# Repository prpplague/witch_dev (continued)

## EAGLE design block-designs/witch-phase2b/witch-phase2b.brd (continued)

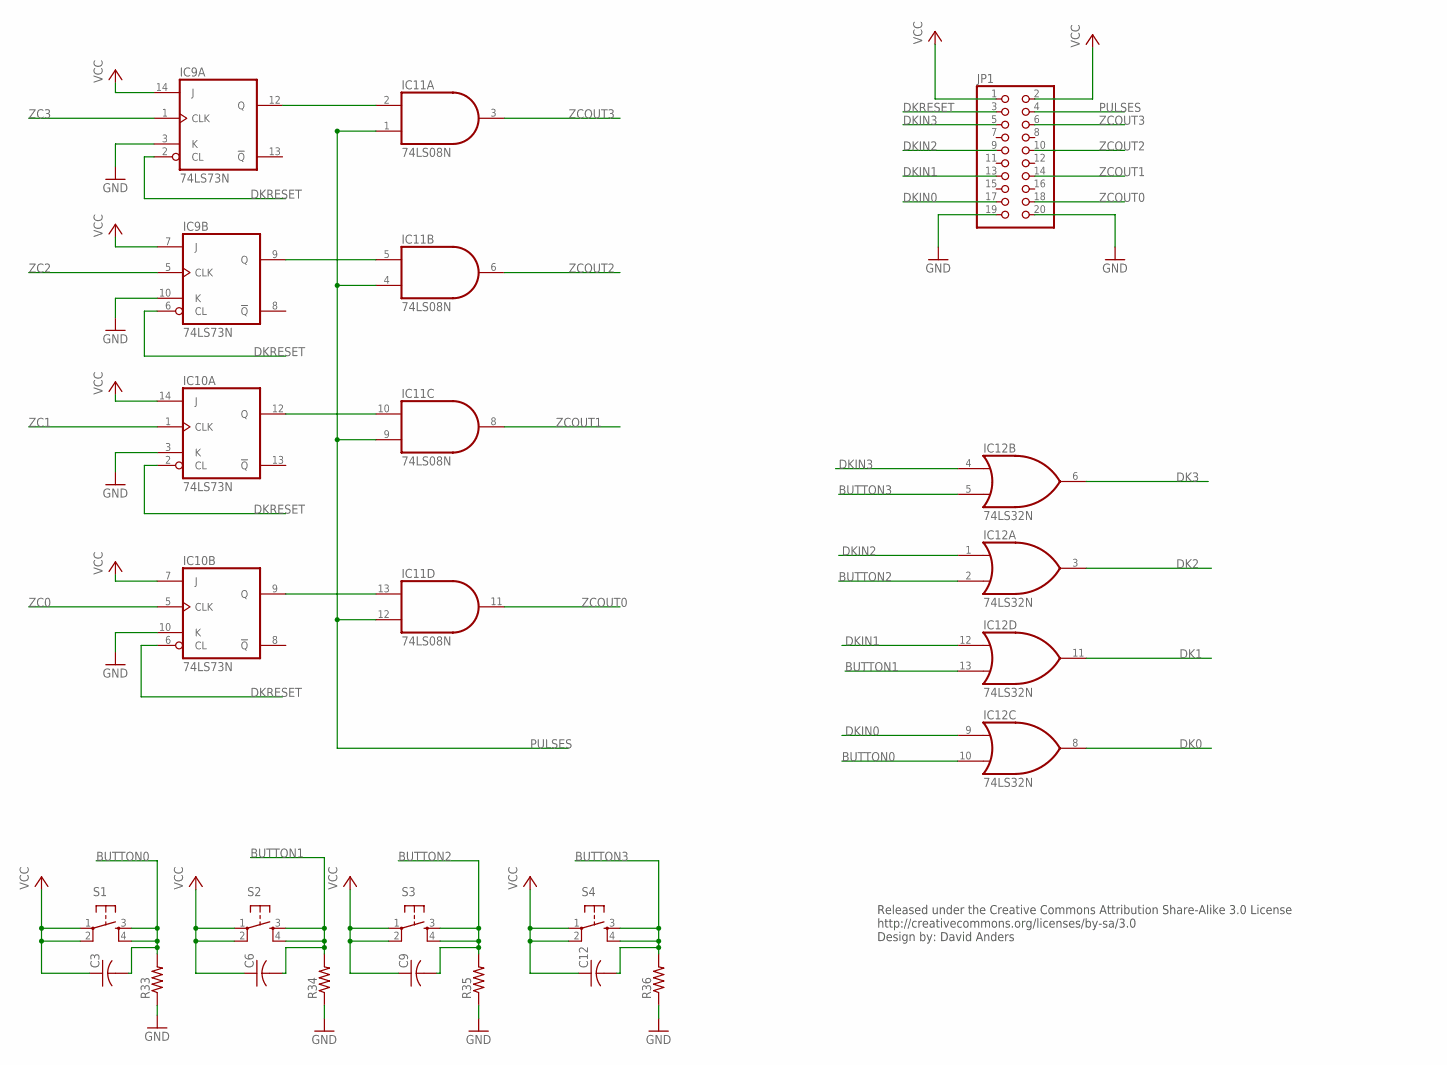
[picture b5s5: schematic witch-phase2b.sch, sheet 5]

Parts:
C3, C6, C9, C12: C-US025-025X050; C025-025X050
IC9, IC10: 74LS73N; DIL14
IC11: 74LS08N; DIL14
IC12: 74LS32N; DIL14
JP1: PINHD-2X10; 2X10
R33, R34, R35, R36: R-US_0204/5; 0204/5
S1, S2, S3, S4: TAC_SWITCHPTH; TACTILE-PTH

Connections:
BUTTON0: C3.2, IC12.10 (I1), R33.2, S1.3, S1.4
BUTTON1: C6.2, IC12.13 (I1), R34.2, S2.3, S2.4
BUTTON2: C9.2, IC12.2 (I1), R35.2, S3.3, S3.4
BUTTON3: C12.2, IC12.5 (I1), R36.2, S4.3, S4.4
DK0: IC12.8 (O); also elsewhere on the board
DK1: IC12.11 (O); also elsewhere on the board
DK2: IC12.3 (O); also elsewhere on the board
DK3: IC12.6 (O); also elsewhere on the board
DKIN0: IC12.9 (I0), JP1.17
DKIN1: IC12.12 (I0), JP1.13
DKIN2: IC12.1 (I0), JP1.9
DKIN3: IC12.4 (I0), JP1.5
DKRESET: IC9.2 (CL), IC9.6 (CL), IC10.2 (CL), IC10.6 (CL), JP1.3
GND: IC9.3 (K), IC9.10 (K), IC10.3 (K), IC10.10 (K), JP1.19, JP1.20, R33.1, R34.1, R35.1, R36.1; also elsewhere on the board
unnamed: IC9.12 (Q), IC11.2 (I1)
unnamed: IC9.9 (Q), IC11.5 (I1)
unnamed: IC10.12 (Q), IC11.10 (I1)
unnamed: IC10.9 (Q), IC11.13 (I1)
PULSES: IC11.1 (I0), IC11.4 (I0), IC11.9 (I0), IC11.12 (I0), JP1.4
VCC: C3.1, IC9.7 (J), IC9.14 (J), IC10.7 (J), IC10.14 (J), JP1.1, JP1.2, S1.1, S1.2, S2.1, S2.2, S3.1, S3.2, S4.1, S4.2; also elsewhere on the board
VCC1: C6.1
VCC2: C9.1
VCC3: C12.1
ZC0: IC10.5 (CLK); also elsewhere on the board
ZC1: IC10.1 (CLK); also elsewhere on the board
ZC2: IC9.5 (CLK); also elsewhere on the board
ZC3: IC9.1 (CLK); also elsewhere on the board
ZCOUT0: IC11.11 (O), JP1.18
ZCOUT1: IC11.8 (O), JP1.14
ZCOUT2: IC11.6 (O), JP1.10
ZCOUT3: IC11.3 (O), JP1.6

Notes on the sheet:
Released under the Creative Commons Attribution Share-Alike 3.0 License http://creativecommons.org/licenses/by-sa/3.0 Design by: David Anders

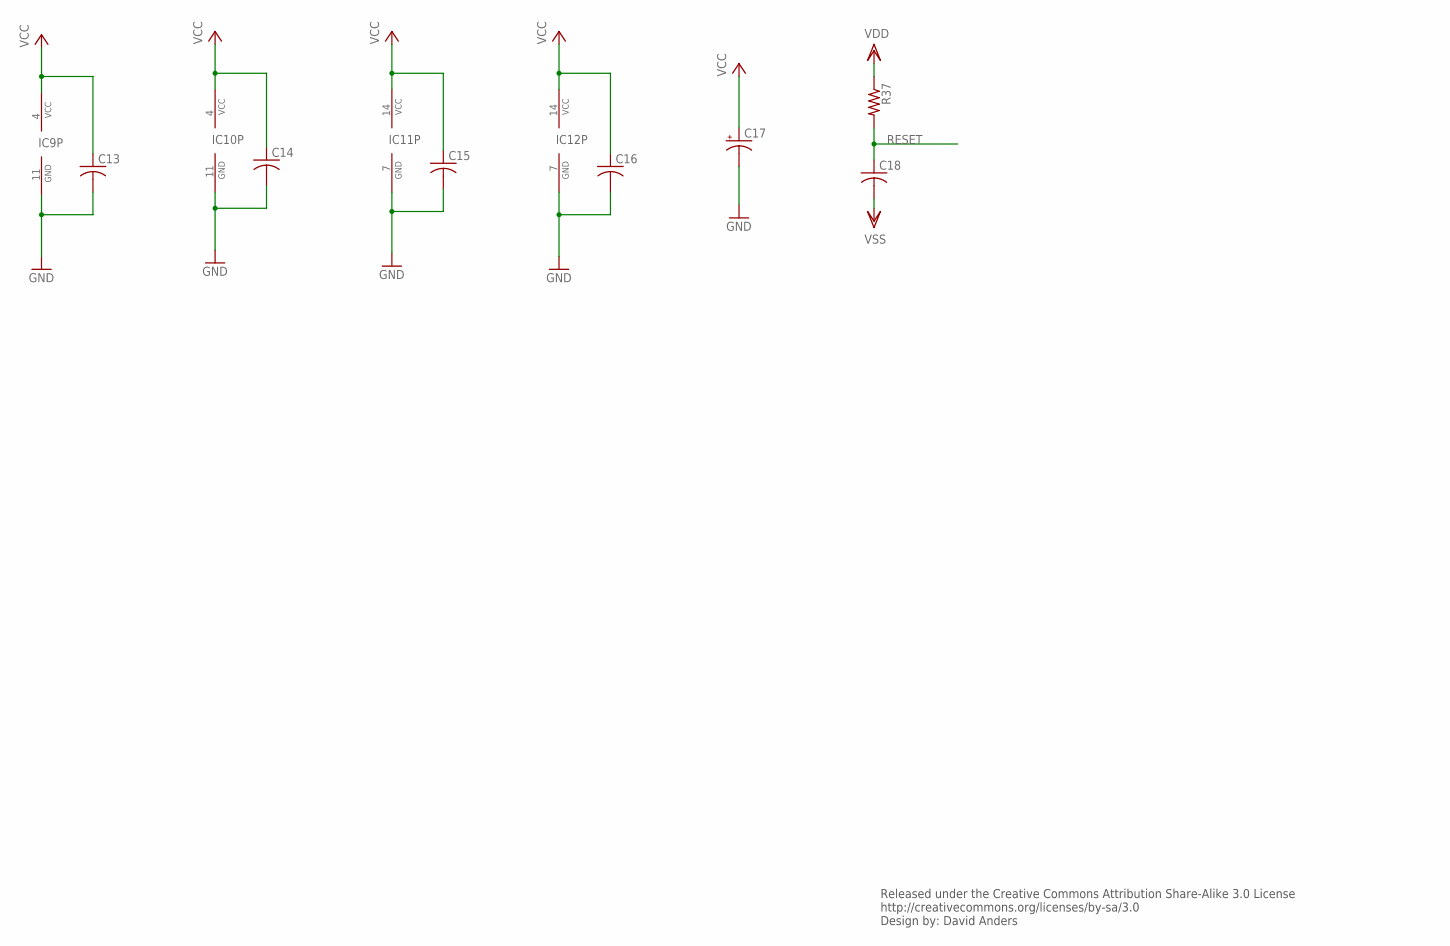
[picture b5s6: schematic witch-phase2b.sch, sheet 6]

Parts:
C13, C14, C15, C16: C-US025-025X050; C025-025X050
C17: CPOL-USE2-5; E2-5
C18: C-US025-040X050; C025-040X050
IC9, IC10: 74LS73N; DIL14
IC11: 74LS08N; DIL14
IC12: 74LS32N; DIL14
R37: R-US_0204/5; 0204/5

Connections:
GND: C13.2, C14.2, C15.2, C16.2, C17.-, IC9.11 (GND), IC10.11 (GND), IC11.7 (GND), IC12.7 (GND); also elsewhere on the board
RESET: C18.1, R37.2; also elsewhere on the board
VCC: C13.1, C14.1, C15.1, C16.1, C17.+, IC9.4 (VCC), IC10.4 (VCC), IC11.14 (VCC), IC12.14 (VCC); also elsewhere on the board
VDD: R37.1
VSS: C18.2

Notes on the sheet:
Released under the Creative Commons Attribution Share-Alike 3.0 License http://creativecommons.org/licenses/by-sa/3.0 Design by: David Anders

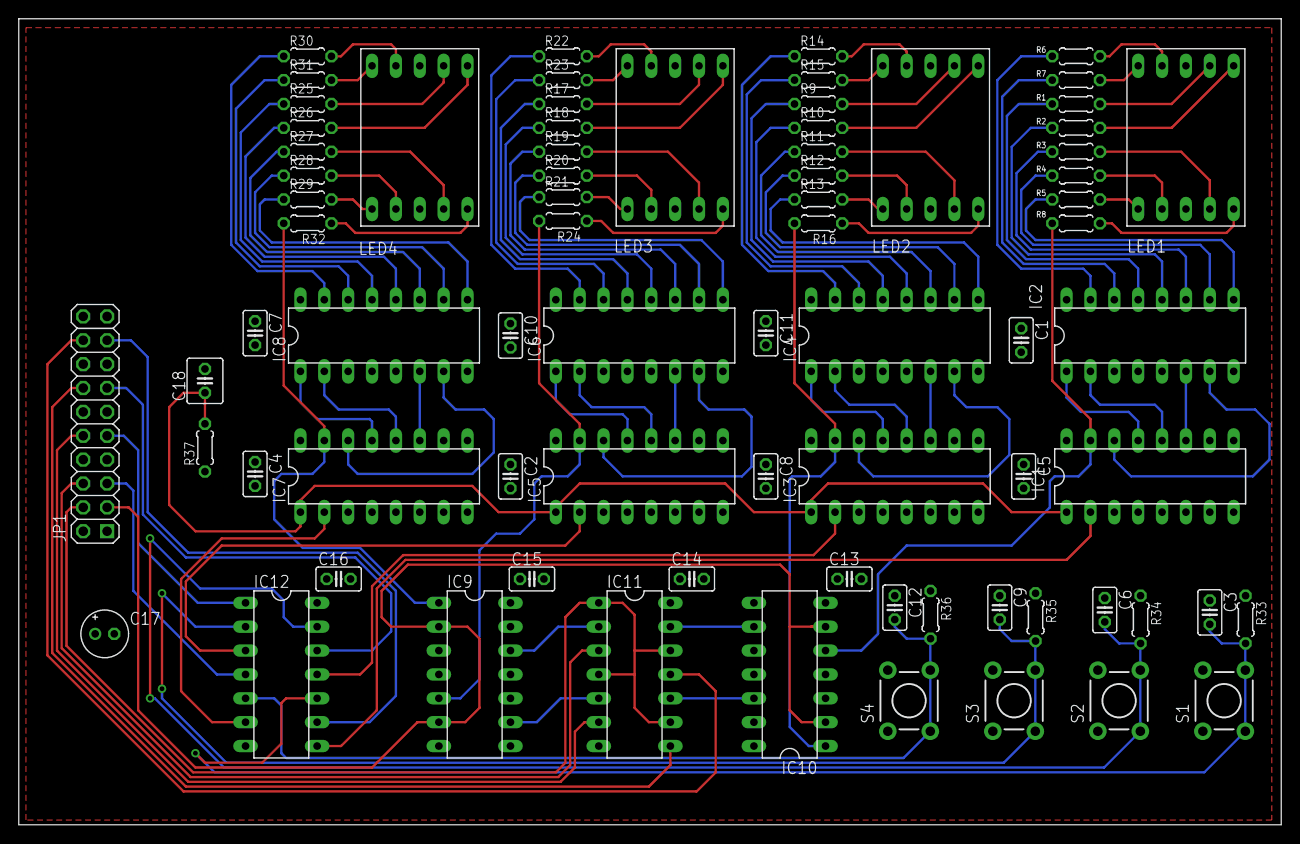
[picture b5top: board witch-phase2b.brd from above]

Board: 2 copper layers, 134.3 x 85.8 mm, 76 parts (0 on the bottom side), 105 nets.

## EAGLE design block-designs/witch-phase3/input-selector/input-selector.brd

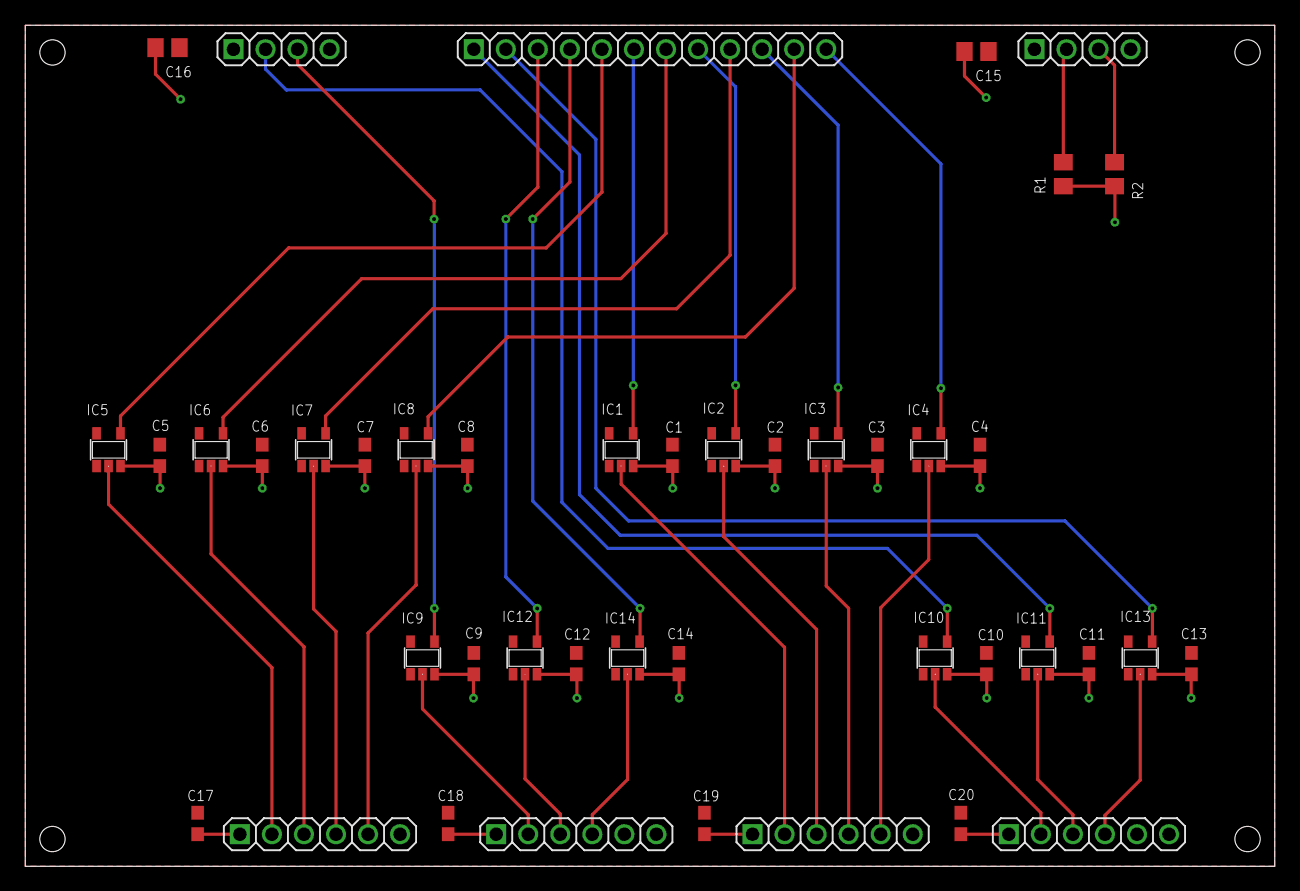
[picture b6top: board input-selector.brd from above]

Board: 2 copper layers, 99.1 x 66.7 mm, 43 parts (0 on the bottom side), 32 nets.

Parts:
C1, C2, C3, C4, C5, C6, C7, C8, C9, C10, C11, C12, C13, C14, C17, C18, C19, C20: C0603
C15, C16: C0805
IC1, IC2, IC3, IC4, IC5, IC6, IC7, IC8, IC9, IC10, IC11, IC12, IC13, IC14: 74LVC1G17DBV; SOT23-5
JP1, JP2, JP3, JP4: 1X06
JP5, JP7: 1X04
JP6: 1X12
R1, R2: R0805

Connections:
GND: C1.2, C2.2, C3.2, C4.2, C5.2, C6.2, C7.2, C8.2, C9.2, C10.2, C11.2, C12.2, C13.2, C14.2, C15.2, C16.2, C17.2, C18.2, C19.2, C20.2, IC1.3, IC2.3, IC3.3, IC4.3, IC5.3, IC6.3, IC7.3, IC8.3, IC9.3, IC10.3, IC11.3, IC12.3, IC13.3, IC14.3, JP1.1, JP2.1, JP3.1, JP4.1, JP5.4, JP7.4, R1.1, R2.1
RCV_ENABLE: JP7.3, R2.2
RCV_ROW0: IC5.4, JP6.5
RCV_ROW1: IC6.4, JP6.7
RCV_ROW2: IC7.4, JP6.9
RCV_ROW3: IC8.4, JP6.11
RCV_SEL0: IC9.4, JP5.3
RCV_SEL1: IC12.4, JP6.3
RCV_SEL2: IC14.4, JP6.4
R_R0: IC5.2, JP4.2
R_R1: IC6.2, JP4.3
R_R2: IC7.2, JP4.4
R_R3: IC8.2, JP4.5
R_S0: IC9.2, JP3.2
R_S1: IC12.2, JP3.3
R_S2: IC14.2, JP3.4
SND_ENABLE: JP7.2, R1.2
SND_ROW0: IC1.4, JP6.6
SND_ROW1: IC2.4, JP6.8
SND_ROW2: IC3.4, JP6.10
SND_ROW3: IC4.4, JP6.12
SND_SEL0: IC10.4, JP5.2
SND_SEL1: IC11.4, JP6.1
SND_SEL2: IC13.4, JP6.2
S_R0: IC1.2, JP2.2
S_R1: IC2.2, JP2.3
S_R2: IC3.2, JP2.4
S_R3: IC4.2, JP2.5
S_S0: IC10.2, JP1.2
S_S1: IC11.2, JP1.3
S_S2: IC13.2, JP1.4
VCC: C1.1, C2.1, C3.1, C4.1, C5.1, C6.1, C7.1, C8.1, C9.1, C10.1, C11.1, C12.1, C13.1, C14.1, C15.1, C16.1, C17.1, C18.1, C19.1, C20.1, IC1.5, IC2.5, IC3.5, IC4.5, IC5.5, IC6.5, IC7.5, IC8.5, IC9.5, IC10.5, IC11.5, IC12.5, IC13.5, IC14.5, JP5.1, JP7.1

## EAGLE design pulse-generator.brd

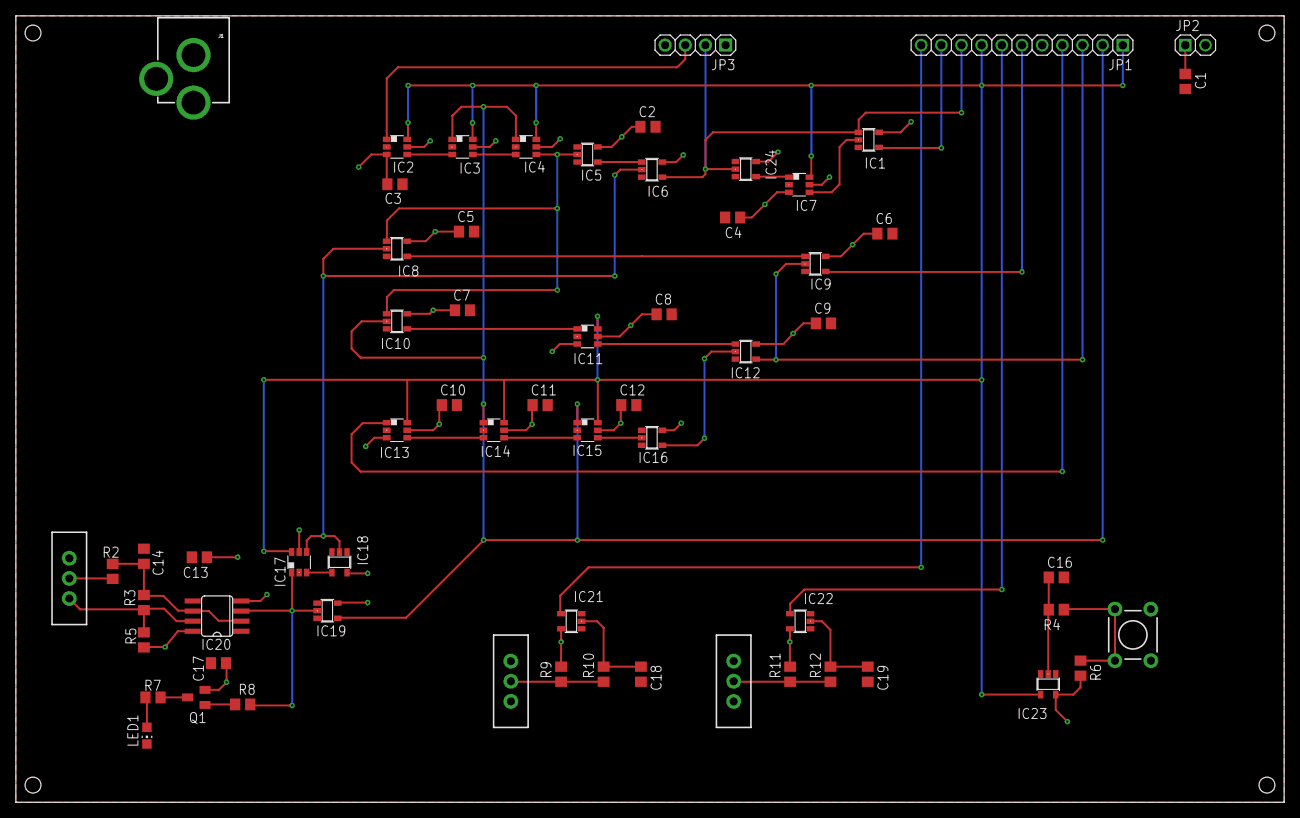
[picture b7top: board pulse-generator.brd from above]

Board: 2 copper layers, 159.8 x 99.1 mm, 63 parts (0 on the bottom side), 40 nets.

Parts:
C1, C2, C4, C5, C8, C10, C13, C14, C16, C17: 10uF; C0805
C3, C6, C7, C9, C11, C12: 1uF; C0805
C18, C19: C0805
IC1, IC6, IC8, IC9, IC10, IC12: 74LVC1G08DBV; SOT23-5
IC2, IC3, IC4, IC7, IC11, IC13, IC14, IC15, IC17: 741G175; DBV_R-PDSO-G6
IC5, IC16, IC18, IC19, IC24: 74LVC1G04DBV; SOT23-5
IC20: NE555D; SO08
IC21, IC22, IC23: 74LVC1G17DBV; SOT23-5
J1: POWER_JACKPTH; POWER_JACK_PTH
JP1: 1X11
JP2: 1X02
JP3: 1X04
LED1: CHIP-LED0805
Q1: MMBT2907ALT1SMD; SOT23-BEC
R2: 8.2K; R0805
R3: 33K; R0805
R4: 10k; R0805
R5, R8: 1K; R0805
R6: 100k; R0805
R7: 270; R0805
R9, R10, R11, R12: R0805
S1, S3, S4: SWITCH-SPDT
S2: TACTILE-PTH

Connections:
9A_PULSE: IC1.4, JP1.10
10A_PULSE: IC1.1, IC6.4, IC24.2, JP1.9, JP3.2
!MCLK: IC3.1, IC4.1, IC10.2, IC14.1, IC15.1, IC19.4, JP1.2
!RST: IC2.6, IC3.6, IC4.6, IC7.6, IC11.6, IC13.6, IC14.6, IC15.6, IC17.6, IC23.4, JP1.1, JP1.8
!TDONE: IC5.4, IC6.1
ADD/COMP: IC22.4, JP1.7
CARRY_DONE: IC13.1, JP1.4
CARRY_OE: IC9.2, IC12.4, JP1.3
CARRY_PULSE: IC9.4, JP1.6
CLR: IC21.4, JP1.11
GND: C1.2, C2.2, C3.2, C4.2, C5.2, C6.2, C7.2, C8.2, C9.2, C10.2, C11.2, C12.2, C13.2, C14.2, C16.2, C17.2, C18.2, C19.2, IC1.3, IC2.2, IC3.2, IC4.2, IC5.3, IC6.3, IC7.2, IC8.3, IC9.3, IC10.3, IC11.2, IC12.3, IC13.2, IC14.2, IC15.2, IC16.3, IC17.2, IC18.3, IC19.3, IC20.1, IC21.3, IC22.3, IC23.3, IC24.3, J1.GND, J1.GNDBREAK, JP2.2, JP3.4, LED1.C, S2.1, S2.2, S3.3, S4.3
MCLK: IC17.1, IC19.2, IC20.3, R8.2
unnamed: IC17.3, IC18.4
unnamed: C14.1, IC20.2, IC20.6, R2.1, R3.1
unnamed: IC20.7, R3.2, R5.1, S1.3
unnamed: R2.2, S1.2
unnamed: Q1.B, R8.1
unnamed: Q1.C, R7.1
unnamed: LED1.A, R7.2
unnamed: IC2.4, IC3.3
unnamed: IC8.4, IC9.1
unnamed: IC13.4, IC14.3
unnamed: IC1.2, IC7.4
unnamed: IC12.2, IC16.4
unnamed: IC3.4, IC4.3
unnamed: IC11.4, IC12.1
unnamed: IC10.4, IC11.1
unnamed: IC14.4, IC15.3
unnamed: IC15.4, IC16.2
unnamed: C16.1, IC23.2, R4.2
unnamed: R4.1, R6.1, S2.3, S2.4
unnamed: C18.1, IC21.2, R10.2
unnamed: R9.1, R10.1, S3.2
unnamed: IC7.1, IC24.4
unnamed: C19.1, IC22.2, R12.2
unnamed: R11.1, R12.1, S4.2
TCLK: IC6.2, IC8.2, IC17.4, IC18.2
TDONE: IC4.4, IC5.2, IC8.1, IC10.1
VCC: C1.1, C2.1, C3.1, C4.1, C5.1, C6.1, C7.1, C8.1, C9.1, C10.1, C11.1, C12.1, C13.1, C17.1, IC1.5, IC2.3, IC2.5, IC3.5, IC4.5, IC5.5, IC6.5, IC7.3, IC7.5, IC8.5, IC9.5, IC10.5, IC11.3, IC11.5, IC12.5, IC13.3, IC13.5, IC14.5, IC15.5, IC16.5, IC17.5, IC18.5, IC19.5, IC20.4, IC20.8, IC21.5, IC22.5, IC23.5, IC24.5, J1.PWR, JP2.1, JP3.1, Q1.E, R5.2, R6.2, R9.2, R11.2
ZC: IC2.1, JP3.3
